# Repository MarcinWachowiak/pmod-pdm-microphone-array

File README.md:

# Pmod PDM microphone array
<div align="justify">
Pmod module with multiple PDM microphones to enable array audio signal processing. Microphones are arranged in a linear array with a spacing of λ/2 at 3 kHz. The Pmod interface enables easy and straightforward evaluation with popular FPGA development boards. Used IM69D130 microphones have matched phase response (±2°) and small sensitivity tolerance (±1dB).
</div>
<br>

  - **Manufactured prototypes**

 **Available configurations**:

  - **2x1**

  - **4x1**

  - **2x2**

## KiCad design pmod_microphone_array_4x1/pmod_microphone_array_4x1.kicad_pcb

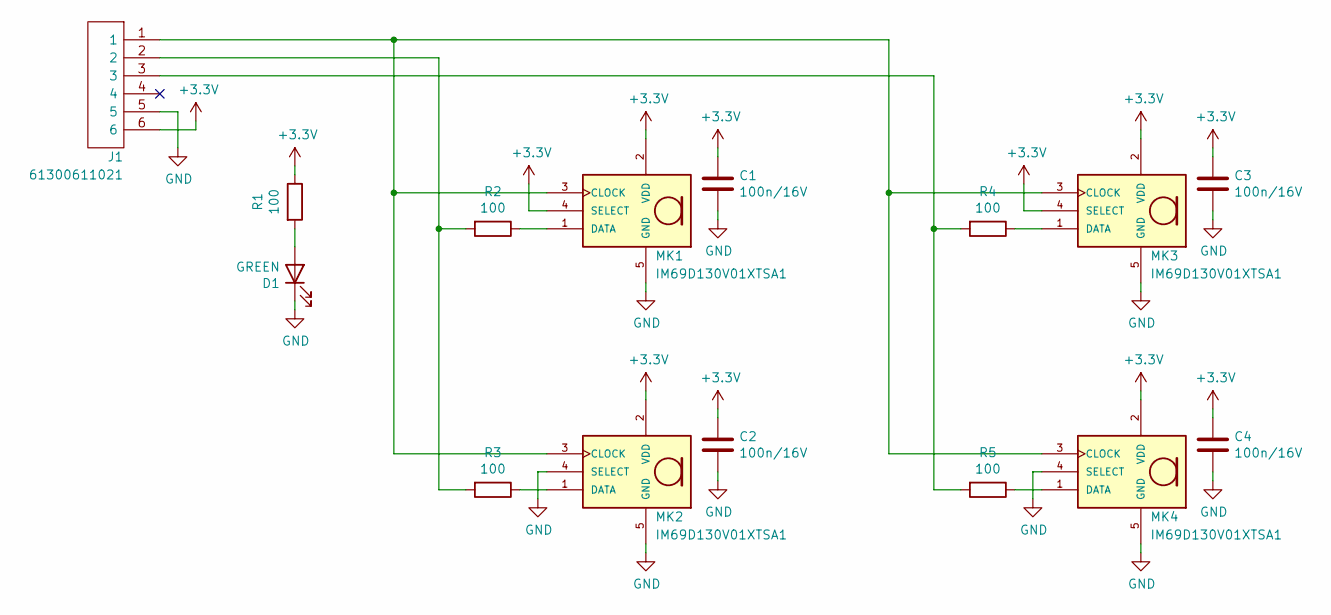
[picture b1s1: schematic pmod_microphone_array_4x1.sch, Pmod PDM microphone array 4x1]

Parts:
C1, C2, C3, C4: 100n/16V; C_0603_1608Metric
D1: GREEN; LED_0603_1608Metric
J1: 61300611021; Manufacturer_Part_Number 61300611021; Mouser Part Number 710-61300611021
MK1, MK2, MK3, MK4: IM69D130V01XTSA1; Manufacturer_Part_Number IM69D130V01XTSA1
R1, R2, R3, R4, R5: 100; R_0603_1608Metric

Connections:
+3V3: C1.1, C2.1, C3.1, C4.1, J1.6, MK1.2 (VDD), MK1.4 (SELECT), MK2.2 (VDD), MK3.2 (VDD), MK3.4 (SELECT), MK4.2 (VDD), R1.1
GND: C1.2, C2.2, C3.2, C4.2, D1.1 (K), J1.5, MK1.5 (GND), MK2.4 (SELECT), MK2.5 (GND), MK3.5 (GND), MK4.4 (SELECT), MK4.5 (GND)
unnamed: D1.2 (A), R1.2
unnamed: J1.1, MK1.3 (CLOCK), MK2.3 (CLOCK), MK3.3 (CLOCK), MK4.3 (CLOCK)
unnamed: J1.2, R2.2, R3.2
unnamed: J1.3, R4.2, R5.2
unnamed: MK1.1 (DATA), R2.1
unnamed: MK2.1 (DATA), R3.1
unnamed: MK3.1 (DATA), R4.1
unnamed: MK4.1 (DATA), R5.1

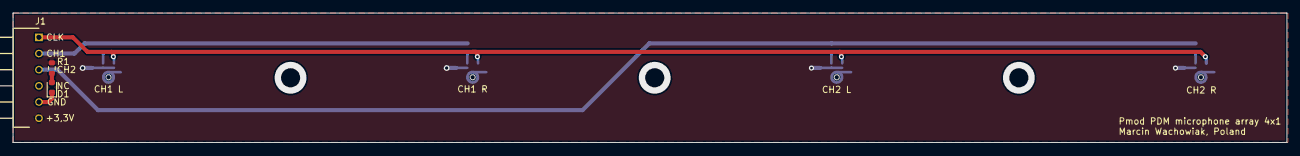
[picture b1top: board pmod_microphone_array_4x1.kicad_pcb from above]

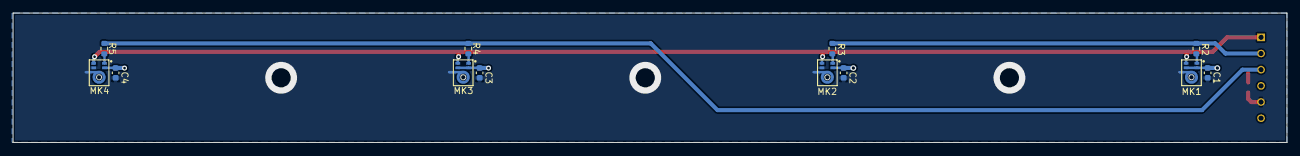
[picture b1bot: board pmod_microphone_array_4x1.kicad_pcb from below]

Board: 2 copper layers, 200.0 x 20.3 mm, 15 parts (12 on the bottom side), 10 nets.

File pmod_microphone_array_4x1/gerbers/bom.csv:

"Source:","/home/marcin/Desktop/Projects/Pmod-PDM-microphone-array/pmod_microphone_array_4x1/pmod_microphone_array_4x1.sch"
"Date:","nie, 26 wrz 2021, 13:46:41"
"Tool:","Eeschema 5.1.10-88a1d61d58~88~ubuntu18.04.1"
"Generator:","/usr/share/kicad/plugins/bom_csv_grouped_by_value_with_fp.py"
"Component Count:","15"
"Ref","Qnty","Value","Cmp name","Footprint","Description","Vendor"
"C1, C2, C3, C4, ","4","100n/16V","C","Capacitor_SMD:C_0603_1608Metric","Unpolarized capacitor",""
"D1, ","1","GREEN","LED","LED_SMD:LED_0603_1608Metric","Light emitting diode",""
"J1, ","1","61300611021","61300611021","pmod_microphone_array:61300611021","Wurth Elektronik WR-PHD 6130, 2.54mm Pitch, 6 Way, 1 Row, Right Angle Pin Header, Through Hole",""
"MK1, MK2, MK3, MK4, ","4","IM69D130V01XTSA1","IM69D130V01XTSA1","pmod_microphone_array:IM69D130V01XTSA1","",""
"R1, R2, R3, R4, R5, ","5","100","R","Resistor_SMD:R_0603_1608Metric","Resistor",""

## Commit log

2022-10-29 Update license
